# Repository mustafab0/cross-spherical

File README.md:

# Cross Spherical gear actuation

#### Original work here:
<p align="center">
  <a href="https://www.youtube.com/watch?v=hhDdfiRCQS4">
    <br>
    Watch the original work on youtube.
  </a>
</p>

# My implementation 
This project involves the use of 3D printing to create various components. The project's centerpiece is the cross-spherical gear, driven by two actuators, each equipped with two motors. While the original design utilized Brushless DC motors from Maxon Motor Inc, this project opts for NEMA17 stepper motors to reduce cost and complexity. The stepper motors are controlled using TMC2208 stepper motor drivers, which are interfaced with Teensy4.0.

<p align="center">
  <br>
</p>

The gear system is driven by actuators, each equipped with two NEMA17 stepper motors. These motors provide the necessary torque and precision for the gear mechanism. The TMC2208 stepper motor drivers, controlled by an overclocked Teensy4.0 microcontroller, ensure smooth and accurate motor operation. The Teensy4.0 is overclocked to 916 MHz to handle all four motors, inverse kinematics, UI, and sensor feedback.

All components are 3D printed on FDM printers.

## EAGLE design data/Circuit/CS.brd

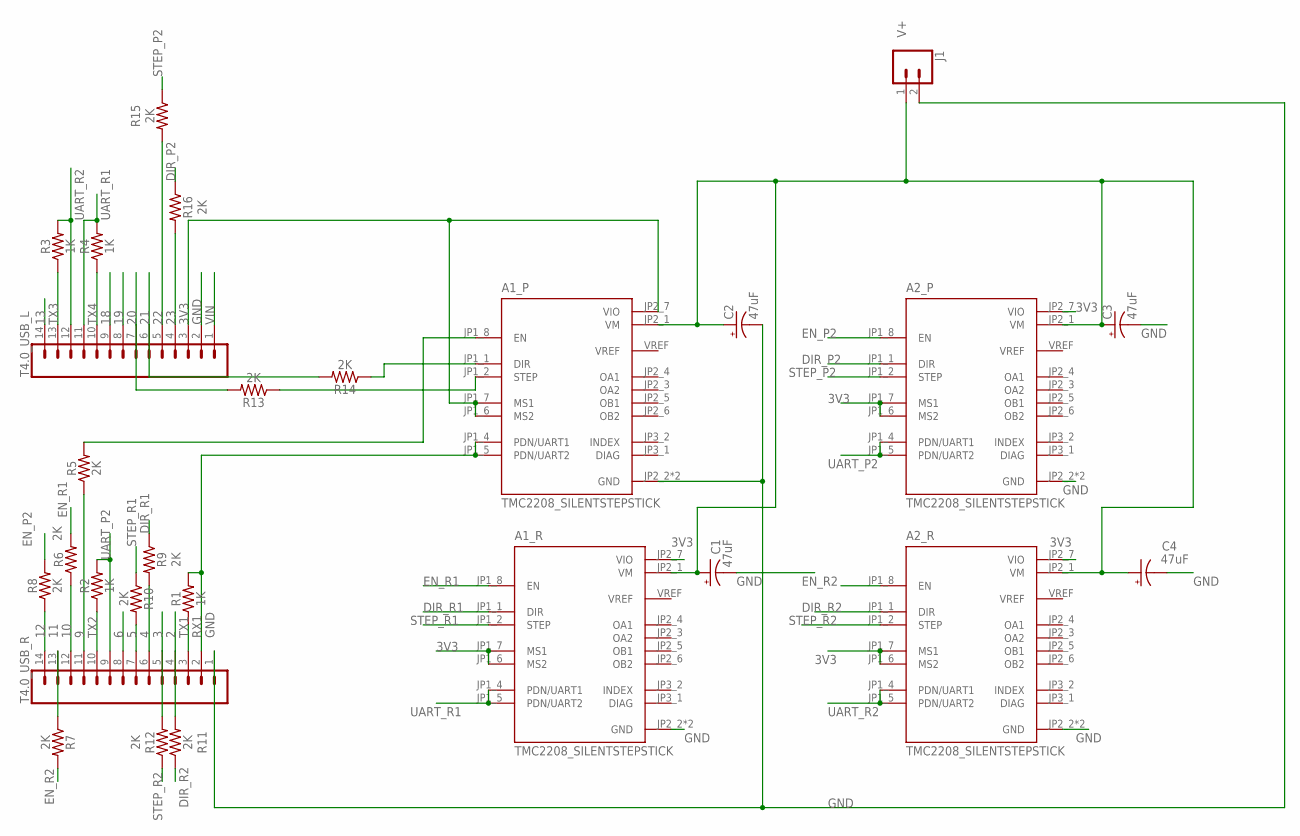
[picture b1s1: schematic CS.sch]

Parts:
A1_P, A1_R, A2_P, A2_R: TMC2208_SILENTSTEPSTICK; MODULE_TMC2208_SILENTSTEPSTICK
C1, C2, C3, C4: 47uF; CPOL-RADIAL-2.5MM-6.5MM
J1: CONN_02; 1X02
R1, R2, R3, R4: 1K; AXIAL-0.3
R5, R6, R7, R8, R9, R10, R11, R12, R13, R14, R15, R16: 2K; AXIAL-0.3
T4.0_USB_L, T4.0_USB_R: CONN_14; 1X14

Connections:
2: R11.P$2 (2), T4.0_USB_R.4
3: R12.P$2 (2), T4.0_USB_R.5
3V3: A1_P.JP1_6 (MS2), A1_P.JP1_7 (MS1), A1_P.JP2_7 (VIO), A1_R.JP1_6 (MS2), A1_R.JP1_7 (MS1), A1_R.JP2_7 (VIO), A2_P.JP1_6 (MS2), A2_P.JP1_7 (MS1), A2_P.JP2_7 (VIO), A2_R.JP1_6 (MS2), A2_R.JP1_7 (MS1), A2_R.JP2_7 (VIO), T4.0_USB_L.3
4: R9.P$2 (2), T4.0_USB_R.6
5: R10.P$2 (2), T4.0_USB_R.7
6: T4.0_USB_R.8
9: R5.P$1 (1), T4.0_USB_R.11
10: R6.P$1 (1), T4.0_USB_R.12
11: R7.P$1 (1), T4.0_USB_R.13
12: R8.P$1 (1), T4.0_USB_R.14
13: T4.0_USB_L.14
18: T4.0_USB_L.9
19: T4.0_USB_L.8
20: R13.P$2 (2), T4.0_USB_L.7
21: R14.P$2 (2), T4.0_USB_L.6
22: R15.P$2 (2), T4.0_USB_L.5
23: R16.P$2 (2), T4.0_USB_L.4
DIR_P2: A2_P.JP1_1 (DIR), R16.P$1 (1)
DIR_R1: A1_R.JP1_1 (DIR), R9.P$1 (1)
DIR_R2: A2_R.JP1_1 (DIR), R11.P$1 (1)
EN_P2: A2_P.JP1_8 (EN), R8.P$2 (2)
EN_R1: A1_R.JP1_8 (EN), R6.P$2 (2)
EN_R2: A2_R.JP1_8 (EN), R7.P$2 (2)
GND: A1_P.JP2_2 (GND), A1_P.JP2_8 (GND), A1_R.JP2_2 (GND), A1_R.JP2_8 (GND), A2_P.JP2_2 (GND), A2_P.JP2_8 (GND), A2_R.JP2_2 (GND), A2_R.JP2_8 (GND), C1.2 (-), C2.2 (-), C3.2 (-), C4.2 (-), J1.2, T4.0_USB_L.2, T4.0_USB_R.1
unnamed: A1_P.JP1_8 (EN), R5.P$2 (2)
unnamed: A1_P.JP2_1 (VM), C2.1 (+)
unnamed: A1_P.JP1_2 (STEP), R13.P$1 (1)
unnamed: A1_P.JP1_1 (DIR), R14.P$1 (1)
RX1: A1_P.JP1_4 (PDN/UART1), A1_P.JP1_5 (PDN/UART2), R1.P$2 (2), T4.0_USB_R.2
STEP_P2: A2_P.JP1_2 (STEP), R15.P$1 (1)
STEP_R1: A1_R.JP1_2 (STEP), R10.P$1 (1)
STEP_R2: A2_R.JP1_2 (STEP), R12.P$1 (1)
TX1: R1.P$1 (1), T4.0_USB_R.3
TX2: R2.P$1 (1), T4.0_USB_R.10
TX3: R3.P$1 (1), T4.0_USB_L.13
TX4: R4.P$1 (1), T4.0_USB_L.10
UART_P2: A2_P.JP1_4 (PDN/UART1), A2_P.JP1_5 (PDN/UART2), R2.P$2 (2), T4.0_USB_R.9
UART_R1: A1_R.JP1_4 (PDN/UART1), A1_R.JP1_5 (PDN/UART2), R4.P$2 (2), T4.0_USB_L.11
UART_R2: A2_R.JP1_4 (PDN/UART1), A2_R.JP1_5 (PDN/UART2), R3.P$2 (2), T4.0_USB_L.12
V+: A1_R.JP2_1 (VM), A2_P.JP2_1 (VM), A2_R.JP2_1 (VM), C1.1 (+), C3.1 (+), C4.1 (+), J1.1
VIN: T4.0_USB_L.1

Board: 2 copper layers, 27 parts (0 on the bottom side), 36 nets, no tracks yet.

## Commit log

2023-06-09 Create TMC_CS.ino
    Teensy code for running TMC2208 driver
2023-06-26 Create main.ino
    latest software
2023-06-28 Create tmp.txt
    Temp
2023-06-28 added eagle files V1 circuit
2023-06-28 reg update
2023-06-28 cleaned up schematic
2023-07-03 urdf folder
2023-07-04 urdf file created
2023-07-04 added csgear environment
2023-07-12 Added code for actuation with UI. Need to add inverse kinematics
2023-07-13 base drawing
2023-07-14 Added IK with beta at 180. NEED TO IMPLEMENT POSITION/POSE TRACKING.
2023-08-14 Trajectory planner notebook
    Updated cs_env.yaml
    Find notebook in code\trajectory
2023-08-19 trajectory planner
2023-08-20 trajectory arduino code
2023-08-21 refactored trajectory code
    Refactored trajectory planning arduino code
    Everything working good
2023-11-07 4 steppers working simultaneously
2023-11-07 added basic motion
2023-11-07 restructured the repo
2024-01-06 open loop roll position tracking
2024-01-07 added set home function
    reworked pitch motion and roll motion function
2024-05-20 added new script with code refactoring
    Refactored basic_motion script and made classes for Stepper motors, actuators and motion controller
2025-05-12 re-organized directory structure
2025-05-12 two stepper test
2025-05-13 4 motor synchronized
2025-05-13 remove build folder from version control
2025-05-13 angular velocity sketch
2025-05-15 choreography
2025-05-15 revised_choreography
2025-05-15 choreographed one stanza
2025-05-15 multistepper choreograph
2025-05-15 multistepper stepper enabled
2025-05-15 added multi standa support
2025-05-15 second stanza added
2025-05-15 stanza1 perfectly synced
2025-05-15 added support for 4 motors
2025-05-16 dance sequence complete
2025-06-07 jetson final

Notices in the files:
parts and their libraries:
SparkFun-Capacitors: Licensing: Creative Commons ShareAlike 4.0 International - https://creativecommons.org/licenses/by-sa/4.0
